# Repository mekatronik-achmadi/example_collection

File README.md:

Examples collection from various works

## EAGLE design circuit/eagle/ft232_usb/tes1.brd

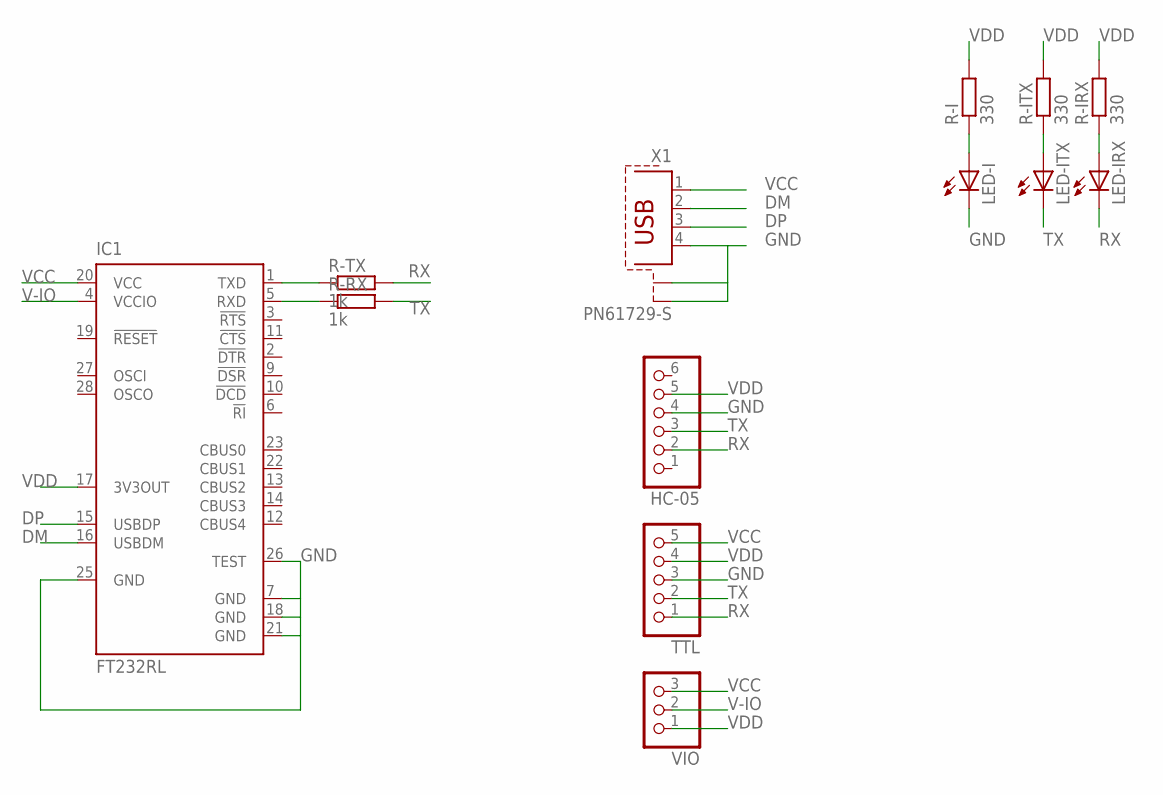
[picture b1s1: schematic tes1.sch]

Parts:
HC-05: PINHD-1X6; 1X06
IC1: FT232RL; SSOP28
LED-I: LED3MM
LED-IRX: LED3MM
LED-ITX: LED3MM
R-I: 330; 0204/7
R-IRX: 330; 0204/7
R-ITX: 330; 0204/7
R-RX: 1k; 0204/7
R-TX: 1k; 0204/7
TTL: PINHD-1X5; 1X05
VIO: PINHD-1X3; 1X03
X1: PN61729-S

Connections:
DM: IC1.16 (USBDM), X1.2
DP: IC1.15 (USBDP), X1.3
GND: HC-05.4, IC1.7 (GND), IC1.18 (GND), IC1.21 (GND), IC1.25 (GND), IC1.26 (TEST), LED-I.K (C), TTL.3, X1.4, X1.S1, X1.S2
unnamed: LED-I.A, R-I.1
unnamed: LED-ITX.A, R-ITX.1
unnamed: LED-IRX.A, R-IRX.1
unnamed: IC1.5 (RXD), R-RX.1
unnamed: IC1.1 (TXD), R-TX.1
RX: HC-05.2, LED-IRX.K (C), R-TX.2, TTL.1
TX: HC-05.3, LED-ITX.K (C), R-RX.2, TTL.2
V-IO: IC1.4 (VCCIO), VIO.2
VCC: IC1.20 (VCC), TTL.5, VIO.3, X1.1
VDD: HC-05.5, IC1.17 (3V3OUT), R-I.2, R-IRX.2, R-ITX.2, TTL.4, VIO.1

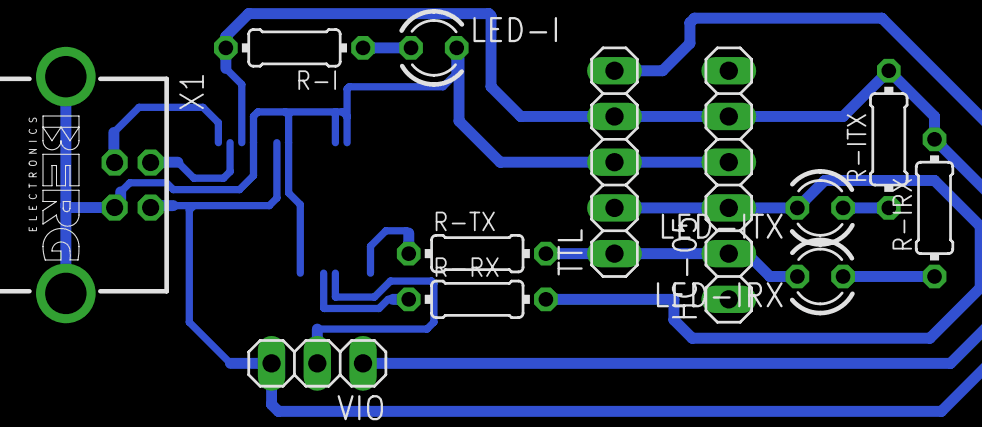
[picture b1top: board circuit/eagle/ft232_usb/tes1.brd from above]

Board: 2 copper layers, 13 parts (1 on the bottom side), 13 nets.

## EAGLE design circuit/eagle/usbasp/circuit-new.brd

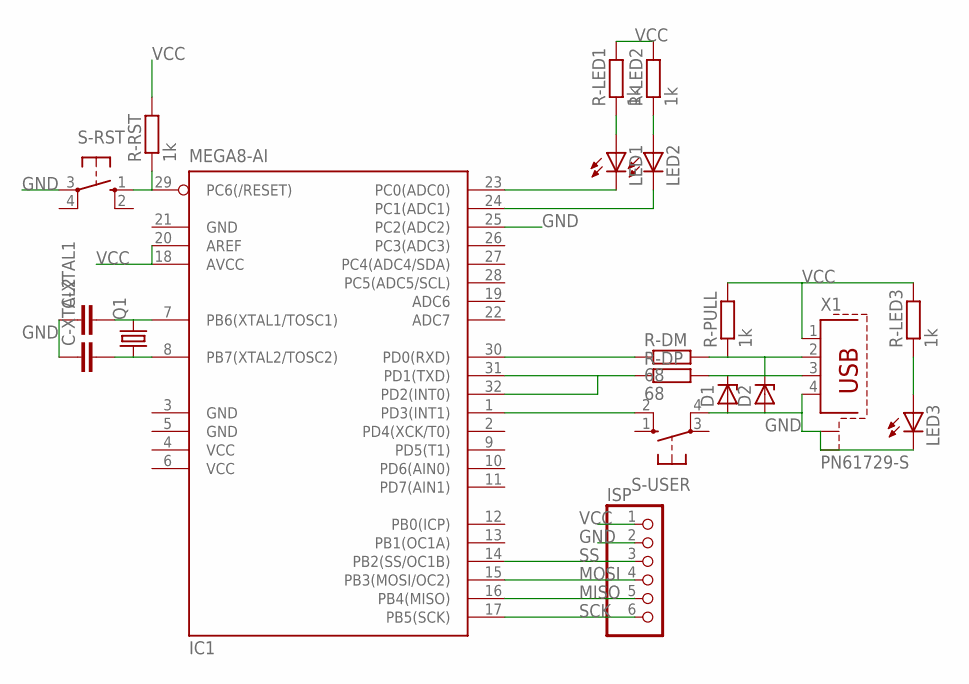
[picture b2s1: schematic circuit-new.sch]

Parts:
C-XTAL1, C-XTAL2: C-EU025-024X044; C025-024X044
D1, D2: ZENER-DIODEDO34-7; DO34Z7
IC1: MEGA8-AI; TQFP32-08
ISP: PINHD-1X6; 1X06
LED1, LED2, LED3: LED3MM
Q1: CRYSTALHC49S; HC49/S
R-DM: 68; 0204/7
R-DP: 68; 0204/7
R-LED1, R-LED2, R-LED3: 1k; 0204/7
R-PULL: 1k; 0204/7
R-RST: 1k; 0204/7
S-RST: 10-XX; B3F-10XX
S-USER: 10-XX; B3F-10XX
X1: PN61729-S

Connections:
GND: C-XTAL1.1, C-XTAL2.1, D1.A, D2.A, IC1.3 (GND), IC1.5 (GND), IC1.21 (GND), IC1.25 (PC2(ADC2)), ISP.2, LED3.K (C), S-RST.3, S-USER.4 (P1), X1.4, X1.S1, X1.S2
MISO: IC1.16 (PB4(MISO)), ISP.5
MOSI: IC1.15 (PB3(MOSI/OC2)), ISP.4
unnamed: IC1.29 (PC6(/RESET)), R-RST.1, S-RST.1 (S)
unnamed: C-XTAL1.2, IC1.7 (PB6(XTAL1/TOSC1)), Q1.2
unnamed: C-XTAL2.2, IC1.8 (PB7(XTAL2/TOSC2)), Q1.1
unnamed: IC1.24 (PC1(ADC1)), LED2.K (C)
unnamed: IC1.23 (PC0(ADC0)), LED1.K (C)
unnamed: IC1.30 (PD0(RXD)), R-DM.1
unnamed: IC1.31 (PD1(TXD)), IC1.32 (PD2(INT0)), R-DP.1
unnamed: IC1.1 (PD3(INT1)), S-USER.2 (S1)
unnamed: LED1.A, R-LED1.1
unnamed: LED2.A, R-LED2.1
unnamed: D1.C, R-DP.2, X1.3
unnamed: D2.C, R-DM.2, R-PULL.1, X1.2
unnamed: LED3.A, R-LED3.1
SCK: IC1.17 (PB5(SCK)), ISP.6
SS: IC1.14 (PB2(SS/OC1B)), ISP.3
VCC: IC1.4 (VCC), IC1.6 (VCC), IC1.18 (AVCC), IC1.20 (AREF), ISP.1, R-LED1.2, R-LED2.2, R-LED3.2, R-PULL.2, R-RST.2, X1.1

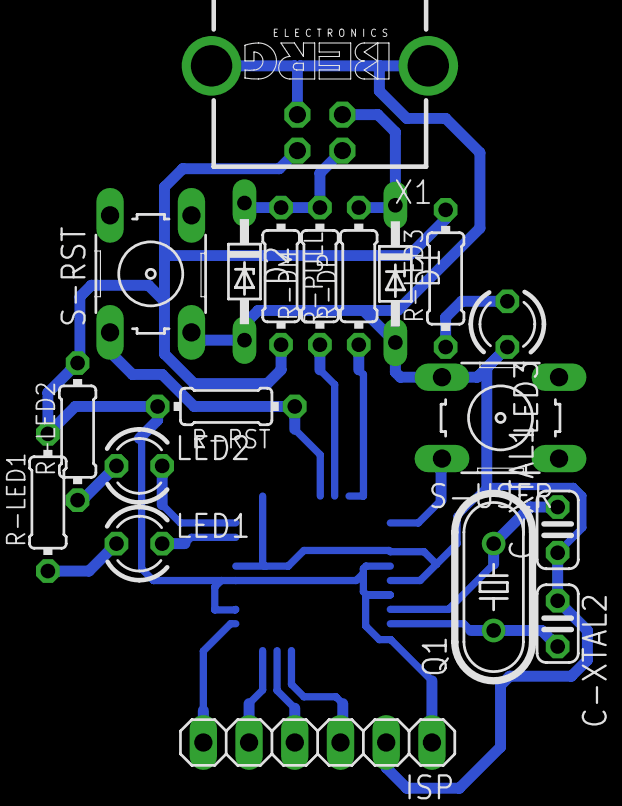
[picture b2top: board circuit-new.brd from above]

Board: 2 copper layers, 20 parts (1 on the bottom side), 19 nets.

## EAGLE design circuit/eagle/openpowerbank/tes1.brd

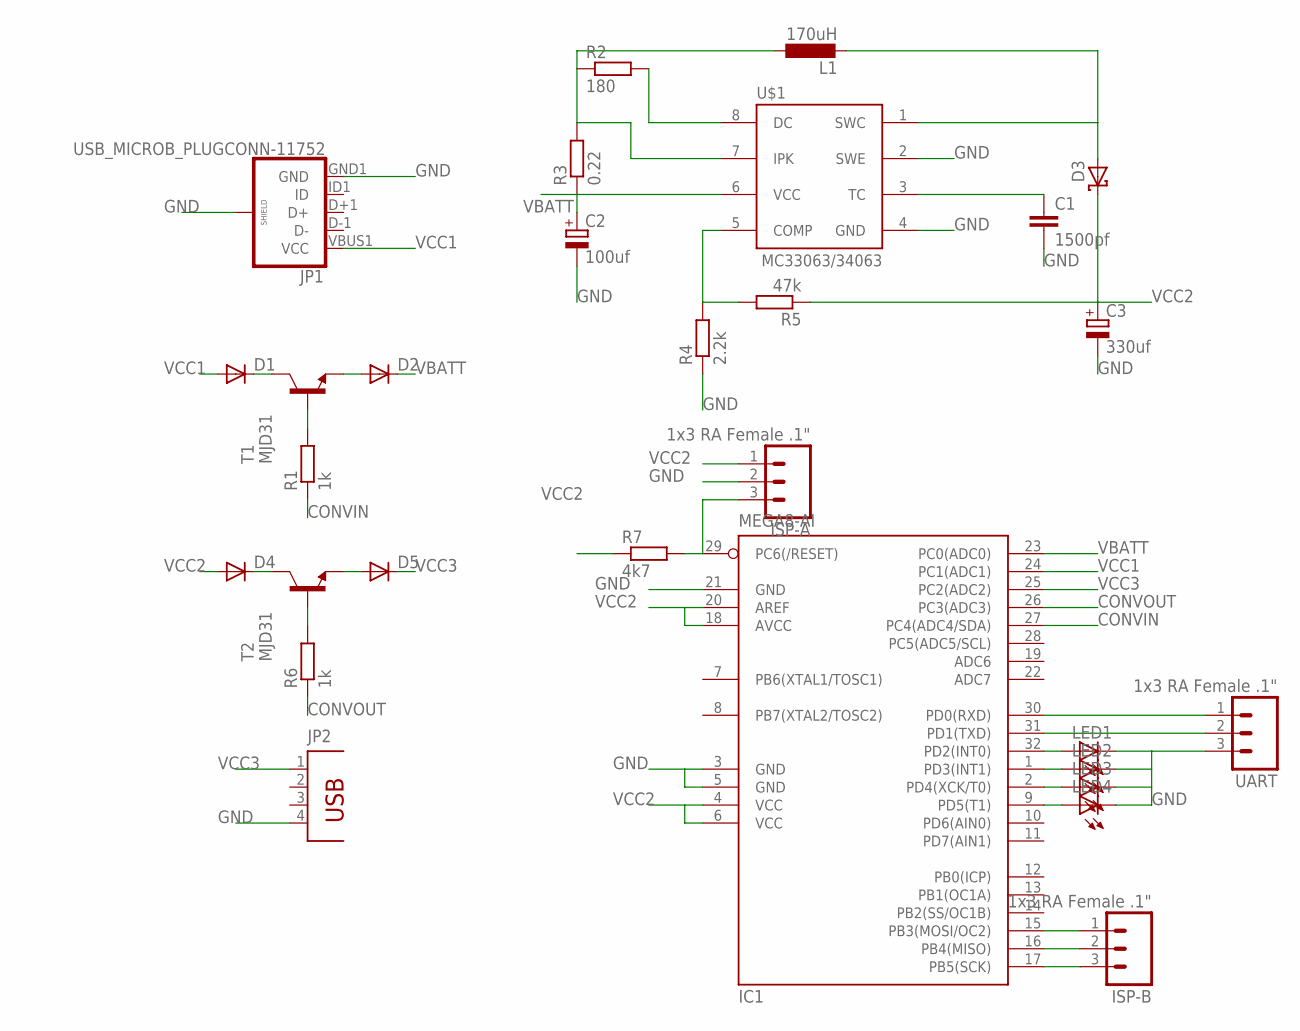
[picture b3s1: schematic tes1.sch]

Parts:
C1: 1500pf; C1206
C2: 100uf; 153CLV-1014
C3: 330uf; 153CLV-1014
D1, D2, D4, D5: DIODE-SMC; SMC
D3: SCHOTTKY-DIODEF126Z12; F126Z12
IC1: MEGA8-AI; TQFP32-08
ISP-A: 1x3 RA Female .1"; 1X03_SMD_RA_FEMALE
ISP-B: 1x3 RA Female .1"; 1X03_SMD_RA_FEMALE
JP1: USB_MICROB_PLUGCONN-11752; USB-B-MICRO-SMD_V03
JP2: PN87520
L1: 170uH; L5650M
LED1, LED2, LED3, LED4: LEDSML1206; SML1206
R1, R6: 1k; R1206
R2: 180; R1206
R3: 0.22; R1206
R4: 2.2k; R1206
R5: 47k; R1206
R7: 4k7; R1206
T1, T2: MJD31; DPAK
U$1: MC33063/MC34063D; SO08
UART: 1x3 RA Female .1"; 1X03_SMD_RA_FEMALE

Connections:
CONVIN: IC1.27 (PC4(ADC4/SDA)), R1.1
CONVOUT: IC1.26 (PC3(ADC3)), R6.1
GND: C1.2, C2.-, C3.-, IC1.3 (GND), IC1.5 (GND), IC1.21 (GND), ISP-A.2, JP1.GND1 (GND), JP1.SHIELD1 (SHIELD), JP1.SHIELD2 (SHIELD), JP1.SHIELD3 (SHIELD), JP2.4, LED1.C, LED2.C, LED3.C, LED4.C, R4.1, U$1.2 (SWE), U$1.4 (GND), UART.3
unnamed: D1.C, T1.4 (C)
unnamed: C1.1, U$1.3 (TC)
unnamed: D2.A, T1.3 (E)
unnamed: L1.1, R2.1, R3.2, U$1.7 (IPK)
unnamed: R1.2, T1.1 (B)
unnamed: R2.2, U$1.8 (DC)
unnamed: R4.2, R5.2, U$1.5 (COMP)
unnamed: D4.C, T2.4 (C)
unnamed: D3.A, L1.2, U$1.1 (SWC)
unnamed: D5.A, T2.3 (E)
unnamed: R6.2, T2.1 (B)
unnamed: IC1.29 (PC6(/RESET)), ISP-A.3, R7.2
unnamed: IC1.17 (PB5(SCK)), ISP-B.3
unnamed: IC1.16 (PB4(MISO)), ISP-B.2
unnamed: IC1.15 (PB3(MOSI/OC2)), ISP-B.1
unnamed: IC1.9 (PD5(T1)), LED4.A
unnamed: IC1.2 (PD4(XCK/T0)), LED3.A
unnamed: IC1.1 (PD3(INT1)), LED2.A
unnamed: IC1.32 (PD2(INT0)), LED1.A
unnamed: IC1.31 (PD1(TXD)), UART.2
unnamed: IC1.30 (PD0(RXD)), UART.1
VBATT: C2.+, D2.C, IC1.23 (PC0(ADC0)), R3.1, U$1.6 (VCC)
VCC1: D1.A, IC1.24 (PC1(ADC1)), JP1.VBUS1 (VCC)
VCC2: C3.+, D3.C, D4.A, IC1.4 (VCC), IC1.6 (VCC), IC1.18 (AVCC), IC1.20 (AREF), ISP-A.1, R5.1, R7.1
VCC3: D5.C, IC1.25 (PC2(ADC2)), JP2.1

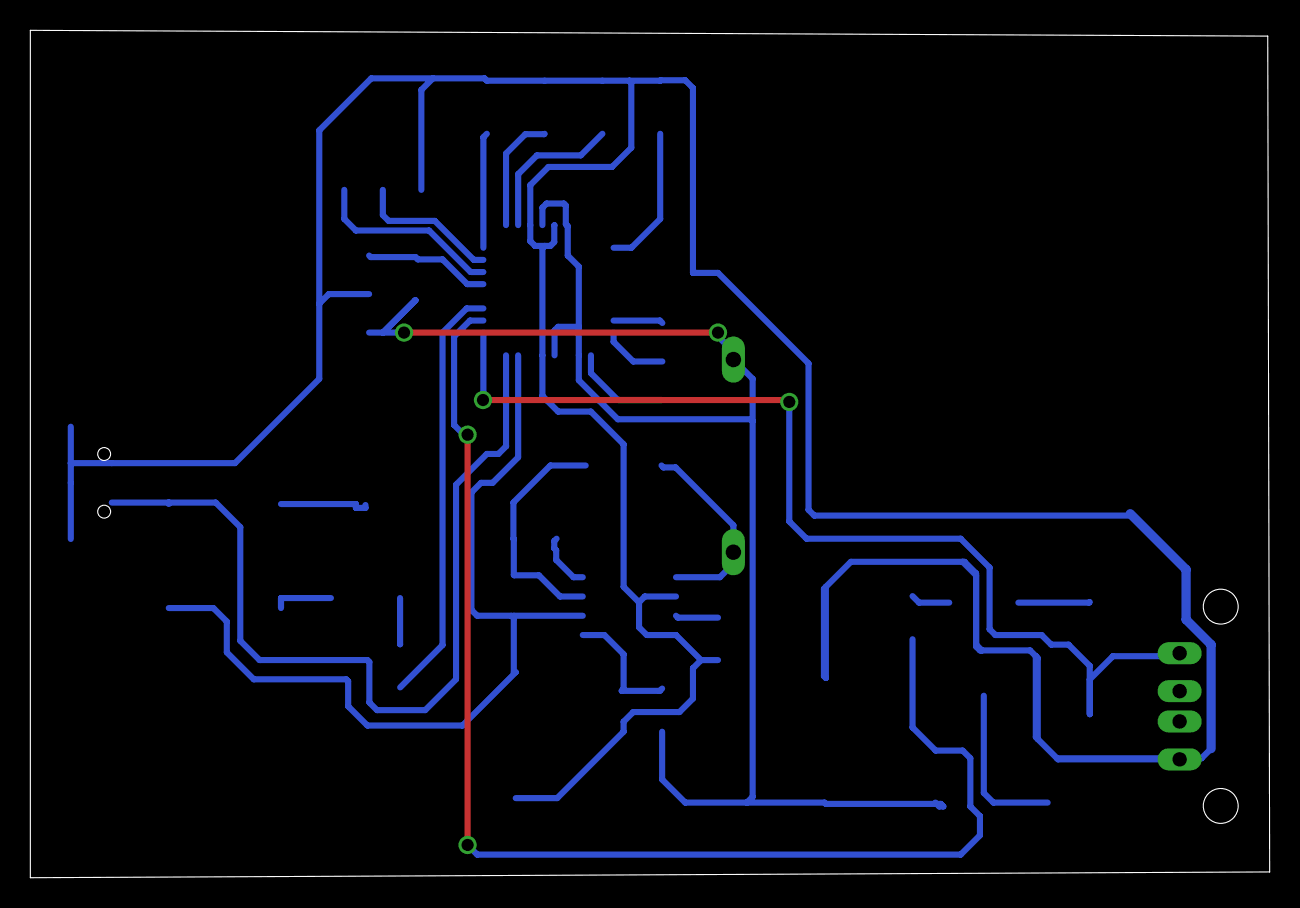
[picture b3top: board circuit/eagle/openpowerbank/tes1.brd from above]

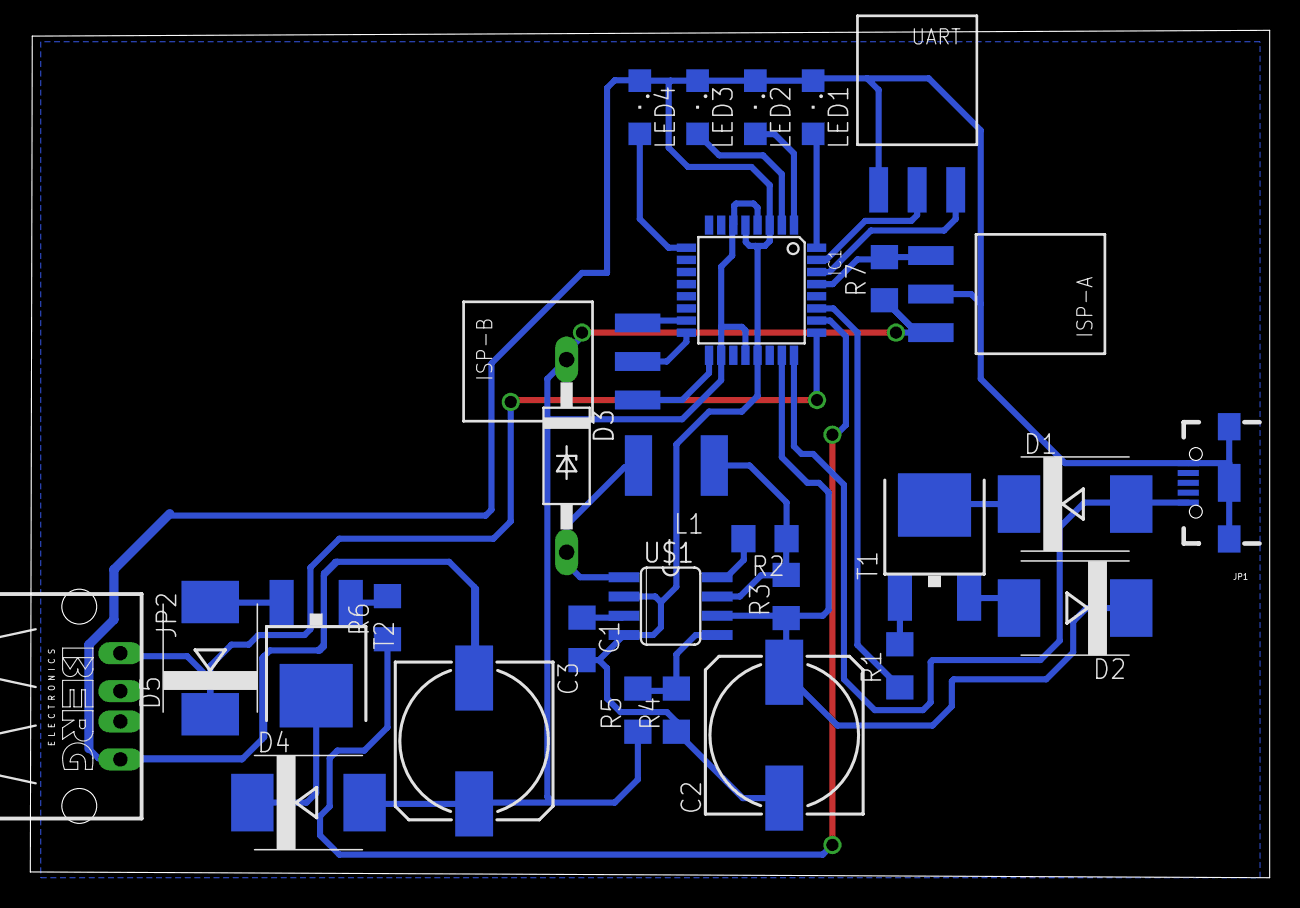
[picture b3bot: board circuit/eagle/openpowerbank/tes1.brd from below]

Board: 2 copper layers, 81.7 x 55.9 mm, 29 parts (29 on the bottom side), 28 nets.

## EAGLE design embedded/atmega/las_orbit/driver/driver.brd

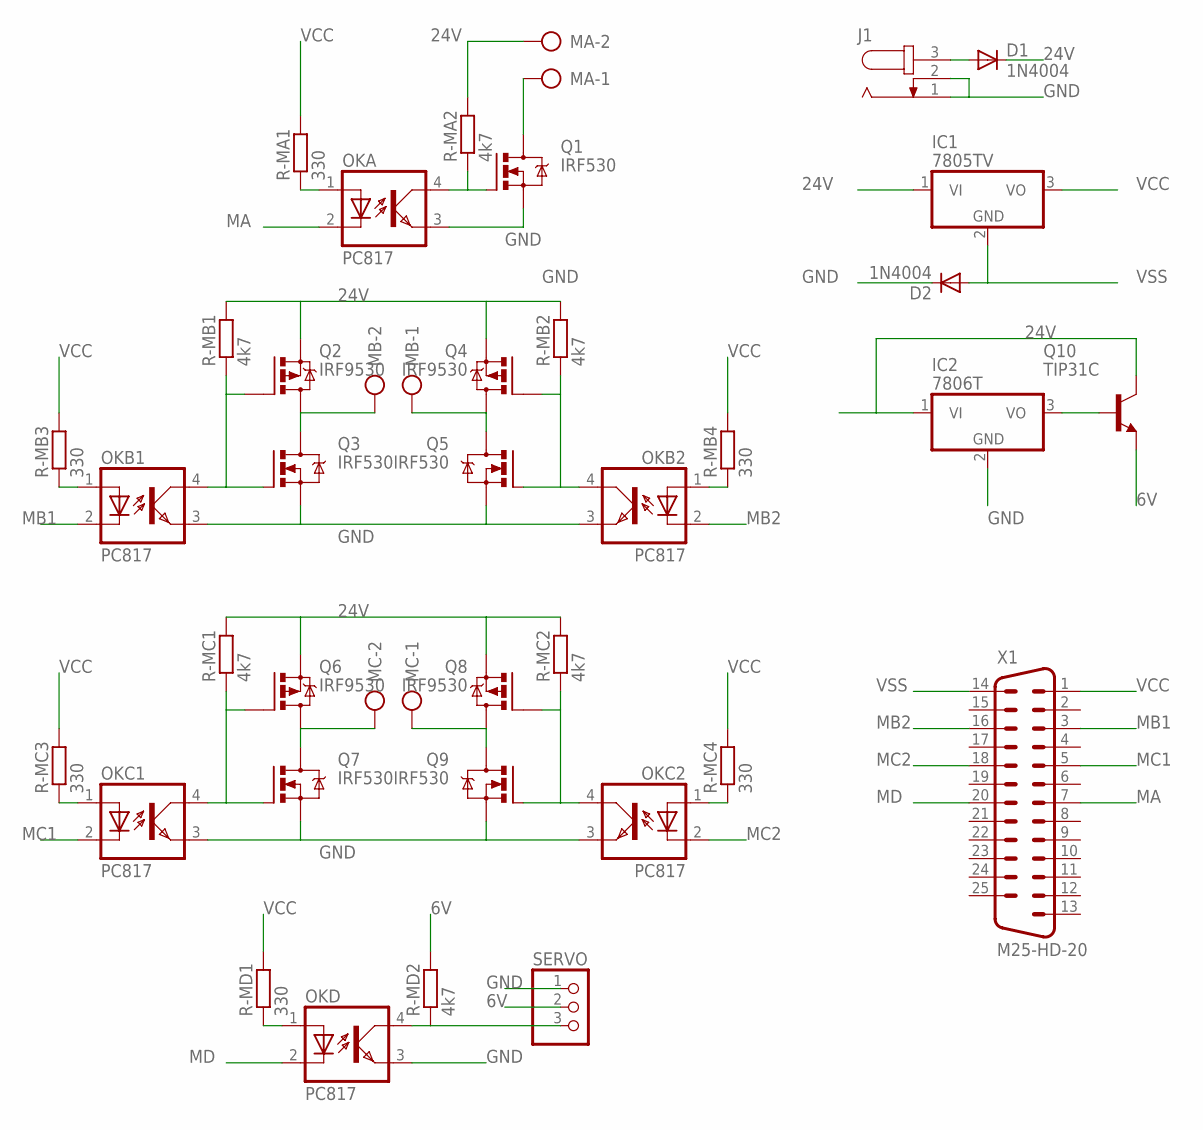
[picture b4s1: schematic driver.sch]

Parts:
D1, D2: 1N4004; DO41-10
IC1: 7805TV; TO220V
IC2: 7806T; TO220H
J1: JACK-PLUG0; SPC4077
MA: AK500/2
MB: AK500/2
MC: AK500/2
OKA: PC817; DIL04
OKB1, OKB2: PC817; DIL04
OKC1, OKC2: PC817; DIL04
OKD: PC817; DIL04
Q1, Q3, Q5, Q7, Q9: IRF530; TO220BV
Q2, Q4, Q6, Q8: IRF9530; TO220BV
Q10: TIP31C; TO220
R-MA1: 330; 0204/7
R-MA2: 4k7; 0204/7
R-MB1, R-MB2: 4k7; 0204/7
R-MB3, R-MB4: 330; 0204/7
R-MC1, R-MC2: 4k7; 0204/7
R-MC3, R-MC4: 330; 0204/7
R-MD1: 330; 0204/7
R-MD2: 4k7; 0204/7
SERVO: PINHD-1X3; 1X03
X1: M25-HD-20

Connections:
6V: Q10.3 (E), R-MD2.2, SERVO.2
24V: D1.C, IC1.1 (VI), IC2.1 (VI), MA.2, Q2.S, Q4.S, Q6.S, Q8.S, Q10.2 (C), R-MA2.2, R-MB1.2, R-MB2.2, R-MC1.2, R-MC2.2
GND: D2.C, IC2.2 (GND), J1.1, J1.2, OKA.3 (EMIT), OKB1.3 (EMIT), OKB2.3 (EMIT), OKC1.3 (EMIT), OKC2.3 (EMIT), OKD.3 (EMIT), Q1.S, Q3.S, Q5.S, Q7.S, Q9.S, SERVO.1
MA: OKA.2 (C), X1.7
MB1: OKB1.2 (C), X1.3
MB2: OKB2.2 (C), X1.16
MC1: OKC1.2 (C), X1.5
MC2: OKC2.2 (C), X1.18
MD: OKD.2 (C), X1.20
MD-SERVO: OKD.4 (COL), R-MD2.1, SERVO.3
unnamed: OKA.4 (COL), Q1.G, R-MA2.1
unnamed: OKA.1 (A), R-MA1.1
unnamed: MB.2, Q2.D, Q3.D
unnamed: MA.1, Q1.D
unnamed: MB.1, Q4.D, Q5.D
unnamed: OKB1.1 (A), R-MB3.1
unnamed: OKB2.1 (A), R-MB4.1
unnamed: MC.2, Q6.D, Q7.D
unnamed: OKB2.4 (COL), Q4.G, Q5.G, R-MB2.1
unnamed: OKB1.4 (COL), Q2.G, Q3.G, R-MB1.1
unnamed: MC.1, Q8.D, Q9.D
unnamed: OKC2.4 (COL), Q8.G, Q9.G, R-MC2.1
unnamed: OKC1.4 (COL), Q6.G, Q7.G, R-MC1.1
unnamed: OKC1.1 (A), R-MC3.1
unnamed: OKC2.1 (A), R-MC4.1
unnamed: OKD.1 (A), R-MD1.1
unnamed: D1.A, J1.3
unnamed: IC2.3 (VO), Q10.1 (B)
VCC: IC1.3 (VO), R-MA1.2, R-MB3.2, R-MB4.2, R-MC3.2, R-MC4.2, R-MD1.2, X1.1
VSS: D2.A, IC1.2 (GND), X1.14

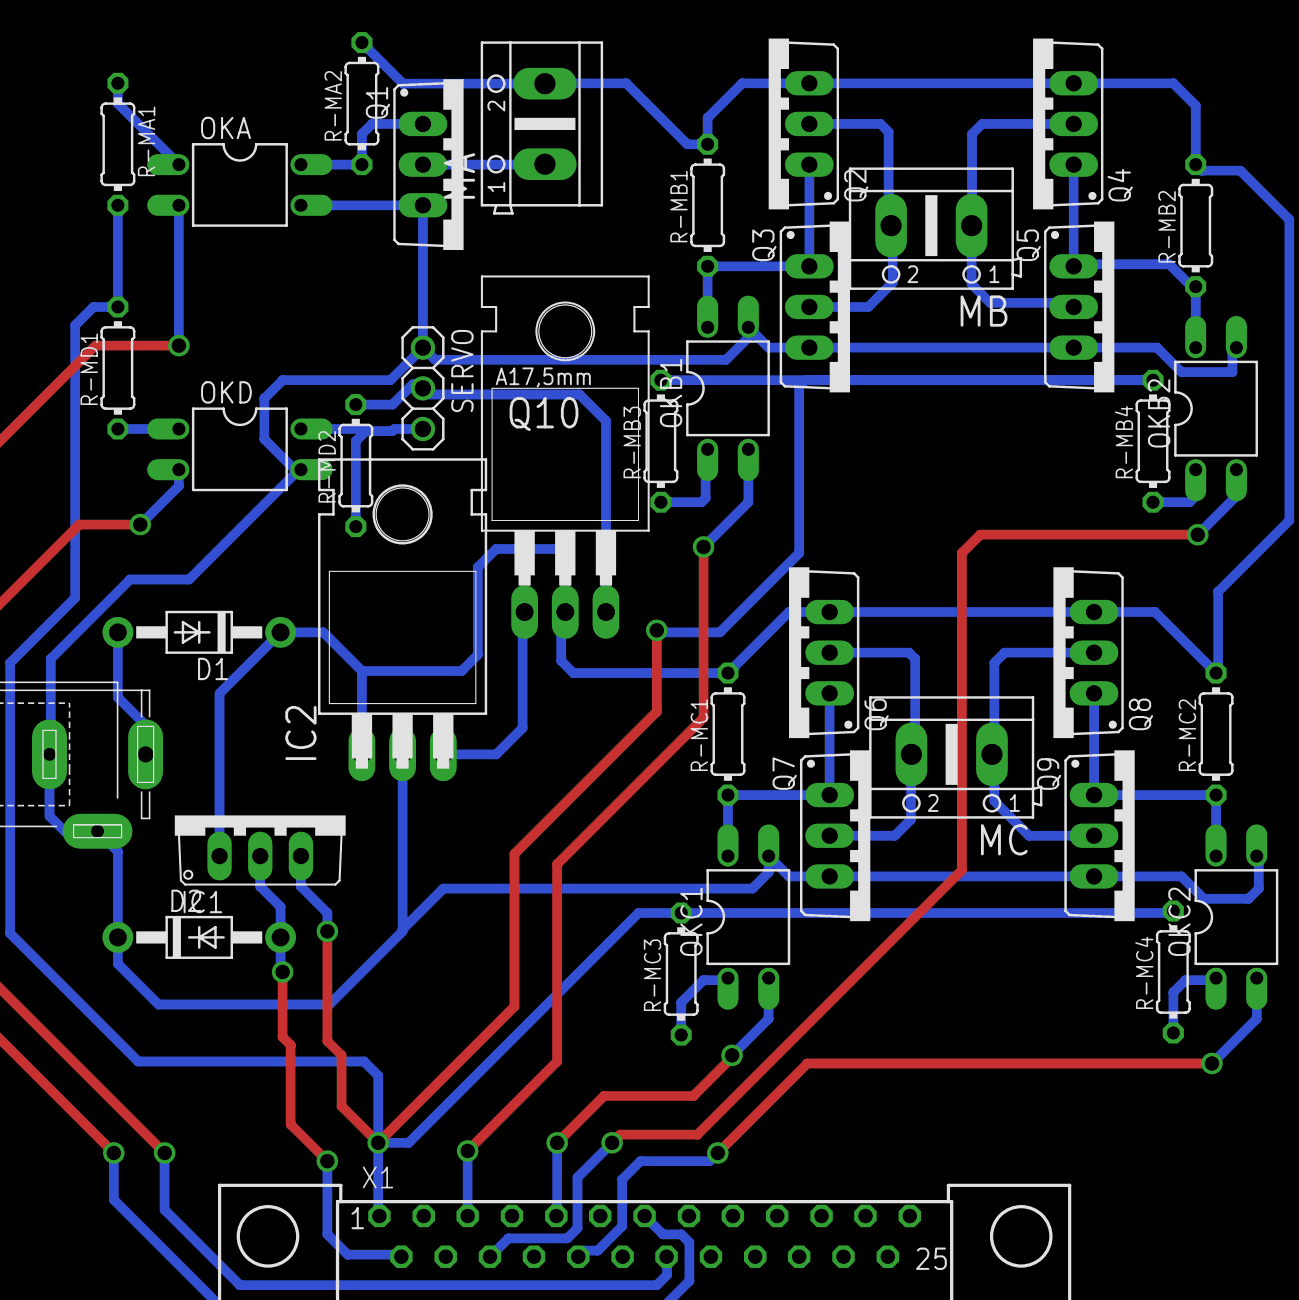
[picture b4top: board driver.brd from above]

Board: 2 copper layers, 38 parts (0 on the bottom side), 30 nets.

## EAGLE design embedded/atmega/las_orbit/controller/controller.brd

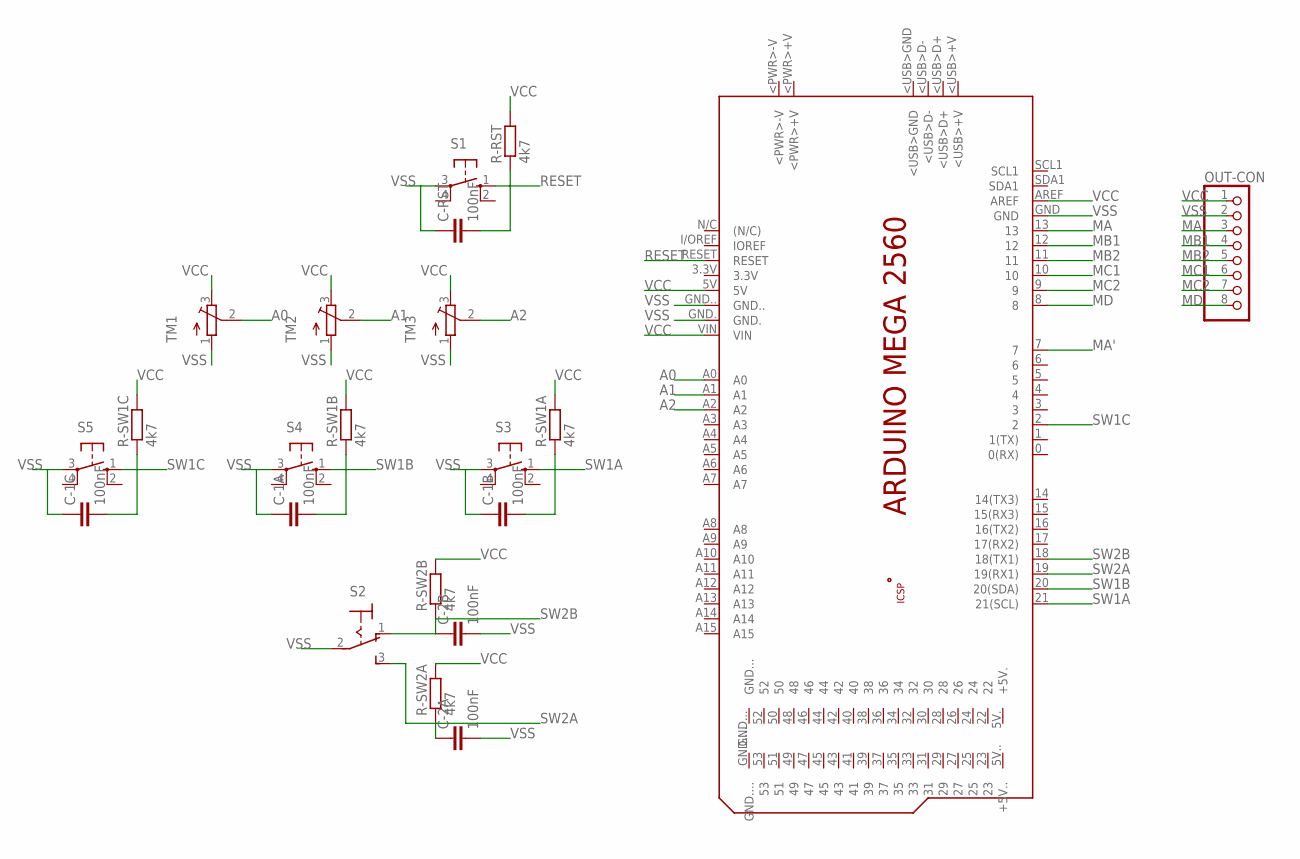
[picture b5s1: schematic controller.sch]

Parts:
C-1A, C-1B, C-1C, C-2A, C-2B: 100nF; C025-024X044
C-RST: 100nF; C025-024X044
OUT-CON: PINHD-1X8; 1X08
PCB1: ARDUINO_MEGA2560
R-RST: 4k7; 0204/7
R-SW1A, R-SW1B, R-SW1C, R-SW2A, R-SW2B: 4k7; 0204/7
S1, S3, S4, S5: 10-XX; B3F-10XX
S2: M9040P
TM1, TM2, TM3: TRIMPOT3386; TRIM-3386

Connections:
A0: PCB1.A0, TM1.2 (S)
A1: PCB1.A1, TM2.2 (S)
A2: PCB1.A2, TM3.2 (S)
MA: OUT-CON.3, PCB1.13
MA': PCB1.7
MB1: OUT-CON.4, PCB1.12
MB2: OUT-CON.5, PCB1.11
MC1: OUT-CON.6, PCB1.10
MC2: OUT-CON.7, PCB1.9
MD: OUT-CON.8, PCB1.8
RESET: C-RST.2, PCB1.RESET, R-RST.1, S1.1 (S)
SW1A: C-1B.2, PCB1.21 (21(SCL)), R-SW1A.1, S3.1 (S)
SW1B: C-1A.2, PCB1.20 (20(SDA)), R-SW1B.1, S4.1 (S)
SW1C: C-1C.2, PCB1.2, R-SW1C.1, S5.1 (S)
SW2A: C-2A.1, PCB1.19 (19(RX1)), R-SW2A.1, S2.3 (S)
SW2B: C-2B.1, PCB1.18 (18(TX1)), R-SW2B.1, S2.1 (O)
VCC: OUT-CON.1, PCB1.5V, PCB1.AREF, PCB1.VIN, R-RST.2, R-SW1A.2, R-SW1B.2, R-SW1C.2, R-SW2A.2, R-SW2B.2, TM1.3 (E), TM2.3 (E), TM3.3 (E)
VSS: C-1A.1, C-1B.1, C-1C.1, C-2A.2, C-2B.2, C-RST.1, OUT-CON.2, PCB1.GND, PCB1.GND., PCB1.GND.., S1.3, S2.2, S3.3, S4.3, S5.3, TM1.1 (A), TM2.1 (A), TM3.1 (A)

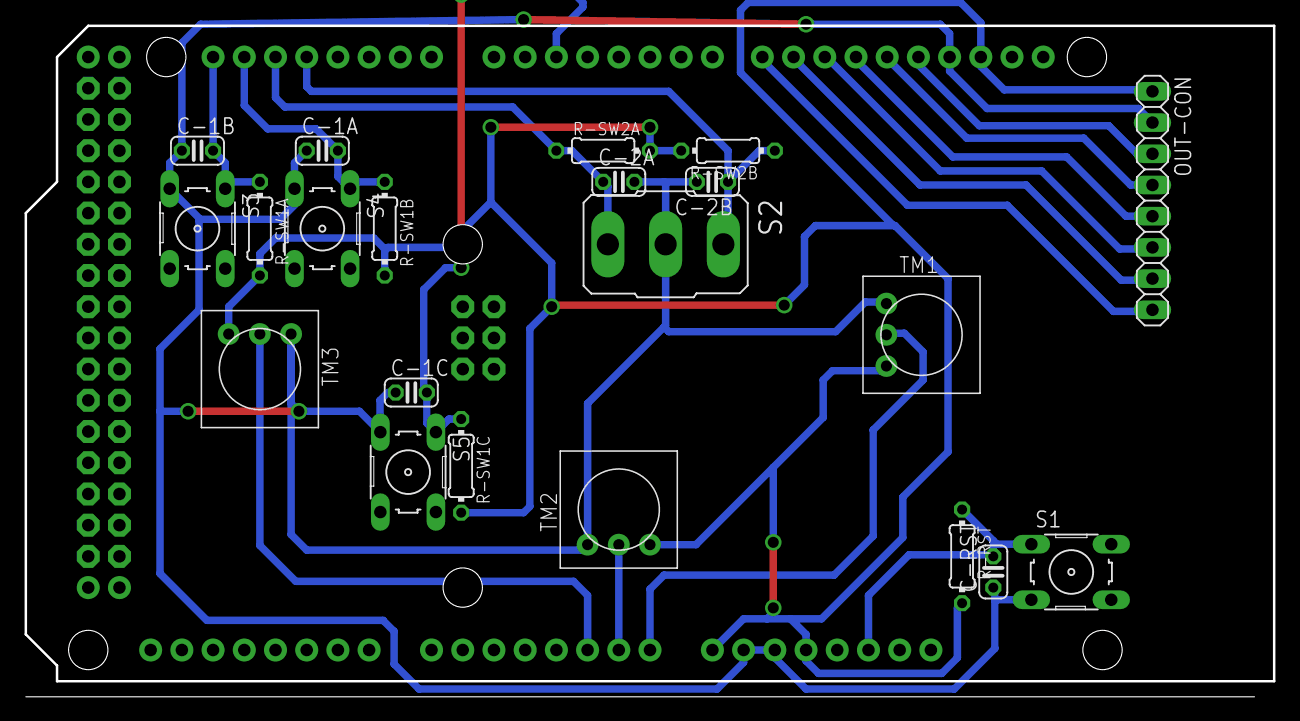
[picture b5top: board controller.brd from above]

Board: 2 copper layers, 101.6 x 54.6 mm, 22 parts (1 on the bottom side), 17 nets.

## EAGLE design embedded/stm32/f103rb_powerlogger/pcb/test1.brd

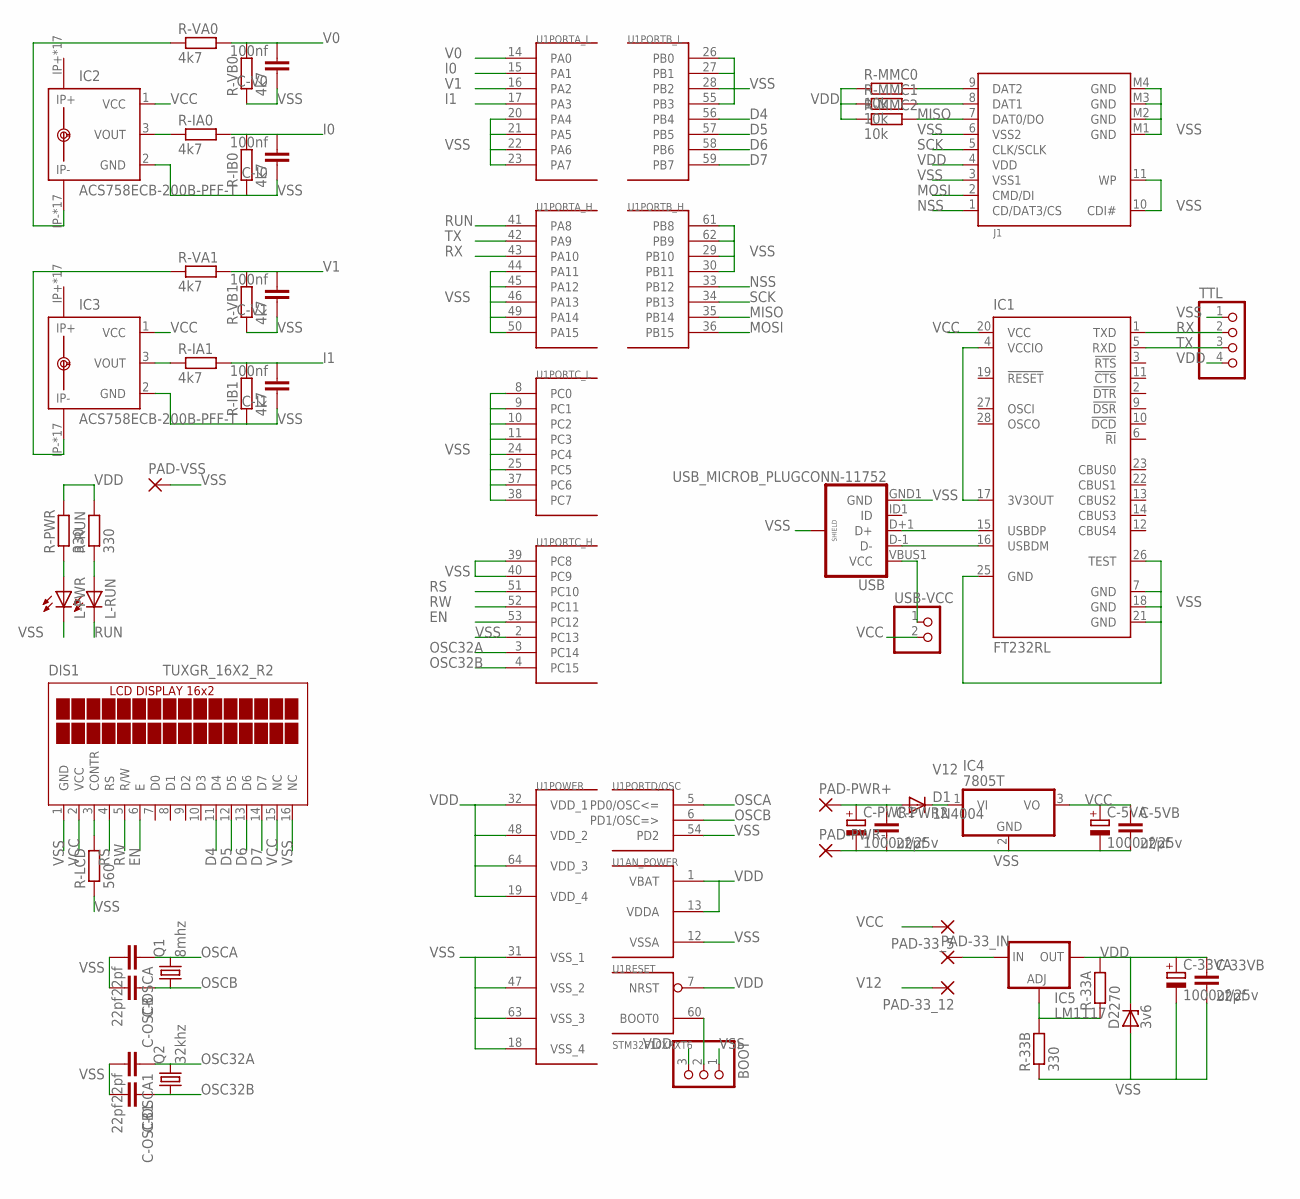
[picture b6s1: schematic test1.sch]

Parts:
BOOT: PINHD-1X3; 1X03
C-5VA, C-33VA: 1000uf/25v; E2-5
C-5VB, C-33VB: 22pf; C1206
C-I0, C-I1: 100nf; C1206
C-OSCA, C-OSCA1: 22pf; C1206
C-OSCB, C-OSCB1: 22pf; C1206
C-PWR1: 1000uf/25v; E2-5
C-PWR2: 22pf; C1206
C-V0, C-V1: 100nf; C1206
D1: 1N4004; DO41-10
D2: 3v6; SMB
DIS1: TUXGR_16X2_R2
IC1: FT232RL; SSOP28
IC2, IC3: ACS758ECB-200B-PFF-T; CB-PFF
IC4: 7805T; TO220H
IC5: LM1117; 317TL
J1: SDCARD; SDCMF-10915W010
L-PWR: LEDSML1206; SML1206
L-RUN: LEDSML1206; SML1206
PAD-33_5, PAD-33_12, PAD-33_IN: 3,81/1,4
PAD-PWR+: 3,81/1,4
PAD-PWR-: 3,81/1,4
PAD-VSS: 3,81/1,4
Q1: 8mhz; HC49/S
Q2: 32khz; TC26V
R-33A: 270; R1206
R-33B: 330; R1206
R-IA0, R-IA1: 4k7; R1206
R-IB0, R-IB1: 4k7; R1206
R-LCD: 560; R1206
R-MMC0, R-MMC1, R-MMC2: 10k; R1206
R-PWR: 330; R1206
R-RUN: 330; R1206
R-VA0, R-VA1: 4k7; R1206
R-VB0, R-VB1: 4k7; R1206
TTL: PINHD-1X4; 1X04
U1: STM32F10XRXT6; TQFP64
USB: USB_MICROB_PLUGCONN-11752; USB-B-MICRO-SMD_V03
USB-VCC: PINHD-1X2; 1X02

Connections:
D4: DIS1.11 (D4), U1.56 (PB4)
D5: DIS1.12 (D5), U1.57 (PB5)
D6: DIS1.13 (D6), U1.58 (PB6)
D7: DIS1.14 (D7), U1.59 (PB7)
EN: DIS1.6 (E), U1.53 (PC12)
I0: C-I0.2, R-IA0.2, R-IB0.2, U1.15 (PA1)
I1: C-I1.2, R-IA1.2, R-IB1.2, U1.17 (PA3)
MISO: J1.7 (DAT0/DO), R-MMC2.2, U1.35 (PB14)
MOSI: J1.2 (CMD/DI), U1.36 (PB15)
unnamed: IC1.16 (USBDM), USB.D-1 (D-)
unnamed: IC1.15 (USBDP), USB.D+1 (D+)
unnamed: IC2.3 (VOUT), R-IA0.1
unnamed: IC2.IP-, IC2.IP-@2 (IP-), IC2.IP-@3 (IP-), IC2.IP-@4 (IP-), IC2.IP-@5 (IP-), IC2.IP-@6 (IP-), IC2.IP-@7 (IP-), IC2.IP-@8 (IP-), IC2.IP-@9 (IP-), IC2.IP-@10 (IP-), IC2.IP-@11 (IP-), IC2.IP-@12 (IP-), IC2.IP-@13 (IP-), IC2.IP-@14 (IP-), IC2.IP-@15 (IP-), IC2.IP-@16 (IP-), IC2.IP-@17 (IP-), R-VA0.1
unnamed: USB.VBUS1 (VCC), USB-VCC.1
unnamed: IC3.3 (VOUT), R-IA1.1
unnamed: IC3.IP-, IC3.IP-@2 (IP-), IC3.IP-@3 (IP-), IC3.IP-@4 (IP-), IC3.IP-@5 (IP-), IC3.IP-@6 (IP-), IC3.IP-@7 (IP-), IC3.IP-@8 (IP-), IC3.IP-@9 (IP-), IC3.IP-@10 (IP-), IC3.IP-@11 (IP-), IC3.IP-@12 (IP-), IC3.IP-@13 (IP-), IC3.IP-@14 (IP-), IC3.IP-@15 (IP-), IC3.IP-@16 (IP-), IC3.IP-@17 (IP-), R-VA1.1
unnamed: DIS1.3 (CONTR), R-LCD.2
unnamed: L-PWR.A, R-PWR.1
unnamed: L-RUN.A, R-RUN.1
unnamed: C-PWR1.+, C-PWR2.1, D1.A, PAD-PWR+.1
unnamed: IC5.3 (IN), PAD-33_IN.1
unnamed: IC5.1 (ADJ), R-33A.1, R-33B.2
unnamed: BOOT.2, U1.60 (BOOT0)
unnamed: J1.8 (DAT1), R-MMC1.2
unnamed: J1.9 (DAT2), R-MMC0.2
NSS: J1.1 (CD/DAT3/CS), U1.33 (PB12)
OSC32A: C-OSCA1.1, Q2.2, U1.3 (PC14)
OSC32B: C-OSCB1.1, Q2.1, U1.4 (PC15)
OSCA: C-OSCA.1, Q1.2, U1.5 (PD0/OSC<=)
OSCB: C-OSCB.1, Q1.1, U1.6 (PD1/OSC=>)
RS: DIS1.4 (RS), U1.51 (PC10)
RUN: L-RUN.C, U1.41 (PA8)
RW: DIS1.5 (R/W), U1.52 (PC11)
RX: IC1.1 (TXD), TTL.2, U1.43 (PA10)
SCK: J1.5 (CLK/SCLK), U1.34 (PB13)
TX: IC1.5 (RXD), TTL.3, U1.42 (PA9)
V0: C-V0.2, R-VA0.2, R-VB0.2, U1.14 (PA0)
V1: C-V1.2, R-VA1.2, R-VB1.2, U1.16 (PA2)
V12: D1.C, IC4.1 (VI), PAD-33_12.1
VCC: C-5VA.+, C-5VB.1, DIS1.2 (VCC), DIS1.15 (NC), IC1.20 (VCC), IC2.1 (VCC), IC3.1 (VCC), IC4.3 (VO), PAD-33_5.1, USB-VCC.2
VDD: BOOT.3, C-33VA.+, C-33VB.1, D2.C, IC1.4 (VCCIO), IC1.17 (3V3OUT), IC5.2 (OUT), J1.4 (VDD), R-33A.2, R-MMC0.1, R-MMC1.1, R-MMC2.1, R-PWR.2, R-RUN.2, TTL.4, U1.1 (VBAT), U1.7 (NRST), U1.13 (VDDA), U1.19 (VDD_4), U1.32 (VDD_1), U1.48 (VDD_2), U1.64 (VDD_3)
VSS: BOOT.1, C-5VA.-, C-5VB.2, C-33VA.-, C-33VB.2, C-I0.1, C-I1.1, C-OSCA.2, C-OSCA1.2, C-OSCB.2, C-OSCB1.2, C-PWR1.-, C-PWR2.2, C-V0.1, C-V1.1, D2.A, DIS1.1 (GND), DIS1.16 (NC), IC1.7 (GND), IC1.18 (GND), IC1.21 (GND), IC1.25 (GND), IC1.26 (TEST), IC2.2 (GND), IC3.2 (GND), IC4.2 (GND), J1.3 (VSS1), J1.6 (VSS2), J1.10 (CDI#), J1.11 (WP), J1.M1 (GND), J1.M2 (GND), J1.M3 (GND), J1.M4 (GND), L-PWR.C, PAD-PWR-.1, PAD-VSS.1, R-33B.1, R-IB0.1, R-IB1.1, R-LCD.1, R-VB0.1, R-VB1.1, TTL.1, U1.2 (PC13), U1.8 (PC0), U1.9 (PC1), U1.10 (PC2), U1.11 (PC3), U1.12 (VSSA), U1.18 (VSS_4), U1.20 (PA4), U1.21 (PA5), U1.22 (PA6), U1.23 (PA7), U1.24 (PC4), U1.25 (PC5), U1.26 (PB0), U1.27 (PB1), U1.28 (PB2), U1.29 (PB10), U1.30 (PB11), U1.31 (VSS_1), U1.37 (PC6), U1.38 (PC7), U1.39 (PC8), U1.40 (PC9), U1.44 (PA11), U1.45 (PA12), U1.46 (PA13), U1.47 (VSS_2), U1.49 (PA14), U1.50 (PA15), U1.54 (PD2), U1.55 (PB3), U1.61 (PB8), U1.62 (PB9), U1.63 (VSS_3), USB.GND1 (GND), USB.SHIELD1 (SHIELD), USB.SHIELD2 (SHIELD), USB.SHIELD3 (SHIELD)

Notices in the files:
parts and their libraries:
SparkFun-Connectors: Licensing: Creative Commons ShareAlike 4.0 International - https://creativecommons.org/licenses/by-sa/4.0
